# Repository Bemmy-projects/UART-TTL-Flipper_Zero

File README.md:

# UART-TTL-Flipper_Zero
TTL to RS232 Serial Adapter for the Flipper Zero

CC BY-NC-SA 4.0
Free for non-commercial use. No warranties or support, express or implicit, are provided. Use as is.

This is a simple UART TTL to RS232 Serial Adapter based on the MAX2323 chip for the Flipper Zero. All necessary files are provided.
After building; the standard values in the Flipper UART Adapter are sufficient for use.

BOM:
1 MAX3232CSE+
5 0.1uF capacitors 0805
1 90deg 1x10 pin strip, 2.54mm pitch
1 D-SUB 9 Connector, 7.70mm offset

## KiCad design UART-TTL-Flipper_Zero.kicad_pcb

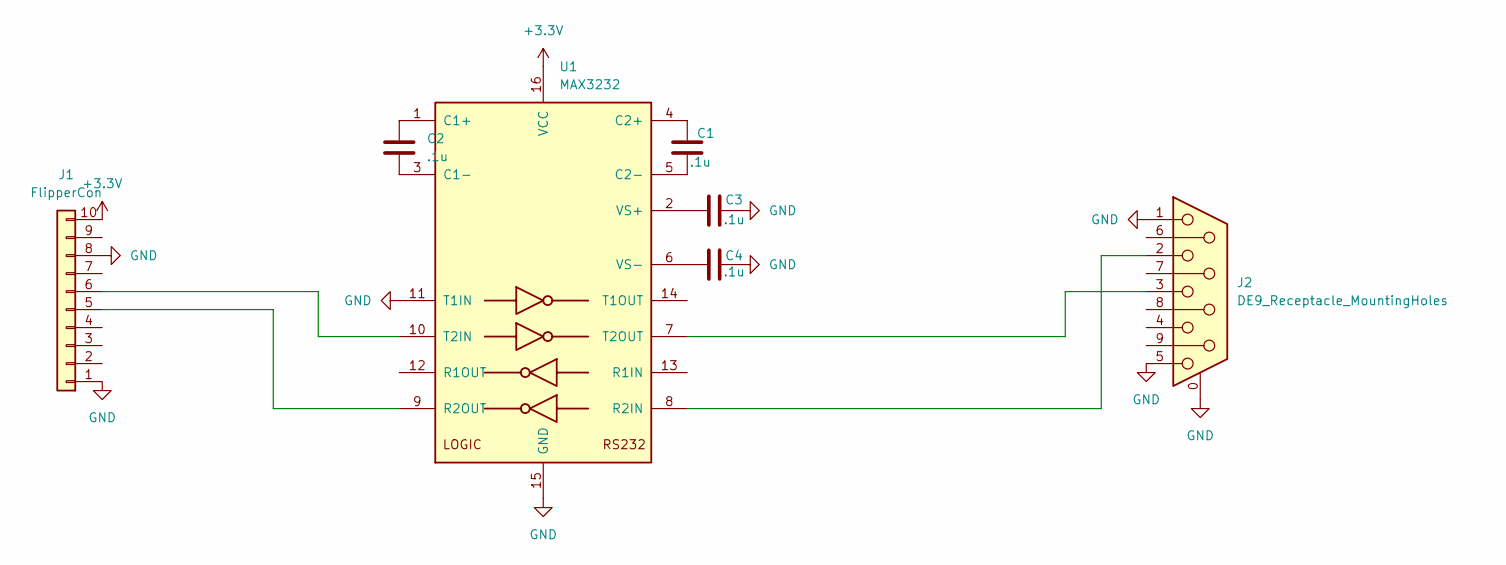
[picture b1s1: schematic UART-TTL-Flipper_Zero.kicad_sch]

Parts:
C1, C2, C3, C4: .1u; C_0805_2012Metric_Pad1.18x1.45mm_HandSolder
J1: FlipperCon; PinHeader_1x10_P2.54mm_Vertical
J2: DE9_Receptacle_MountingHoles; DSUB-9_Female_Horizontal_P2.77x2.84mm_EdgePinOffset7.70mm_H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
U1: MAX3232; SOIC127P600X175-16N

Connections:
+3.3V: J1.10, U1.16 (VCC)
GND: C3.1, C4.2, J1.1, J1.8, J2.0 (PAD), J2.1, J2.5, U1.11 (T1IN), U1.15 (GND)
unnamed: J1.5, U1.9 (R2OUT)
unnamed: J1.6, U1.10 (T2IN)
unnamed: C2.1, U1.1 (C1+)
unnamed: C2.2, U1.3 (C1-)
unnamed: C1.1, U1.4 (C2+)
unnamed: C1.2, U1.5 (C2-)
unnamed: J2.2, U1.8 (R2IN)
unnamed: J2.3, U1.7 (T2OUT)
unnamed: C3.2, U1.2 (VS+)
unnamed: C4.1, U1.6 (VS-)

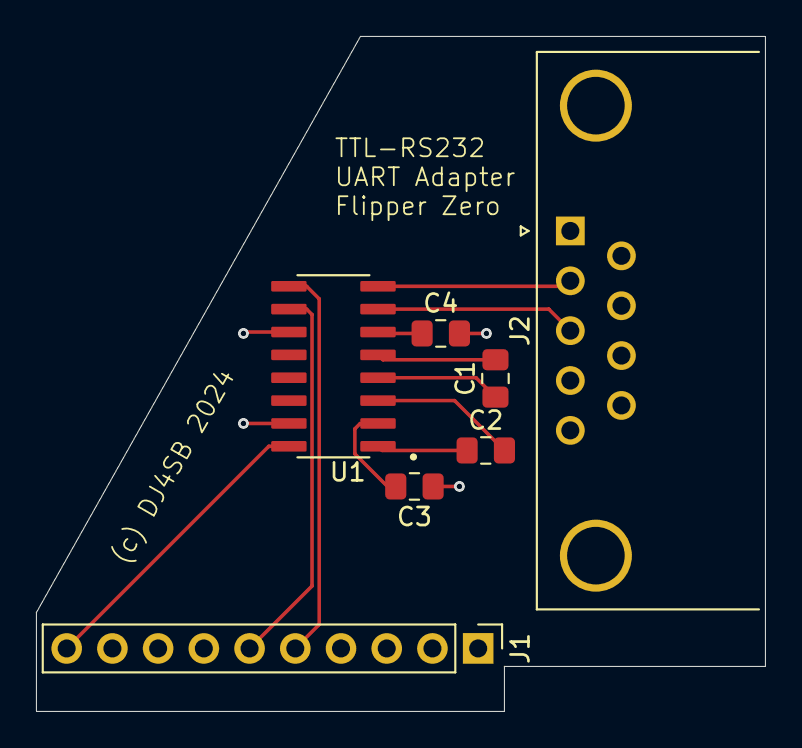
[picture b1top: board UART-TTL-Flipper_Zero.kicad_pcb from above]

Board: 2 copper layers, 40.5 x 37.5 mm, 7 parts (0 on the bottom side), 12 nets.

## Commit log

2024-07-09 Update README.md
    Wrote README
2024-07-09 Inital commit
2024-07-09 Clarify README.md
